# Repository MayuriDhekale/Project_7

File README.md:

# Project_7
<br>
<b>4-Layer STM32F407 Industrial Development Board</b>
<br>
Designed and developed a custom 4-layer STM32F407VGT6 development board intended as a flexible platform for embedded and industrial communication applications.
The board uses the STM32F407VGT6 microcontroller and includes USB Type-C, CAN, RS-485, UART, I²C, SPI, SWD, and GPIO interfaces. It also has a 3.3V power supply, reset and boot circuit, 8 MHz and 32.768 kHz crystals, and expansion headers for connecting external devices.

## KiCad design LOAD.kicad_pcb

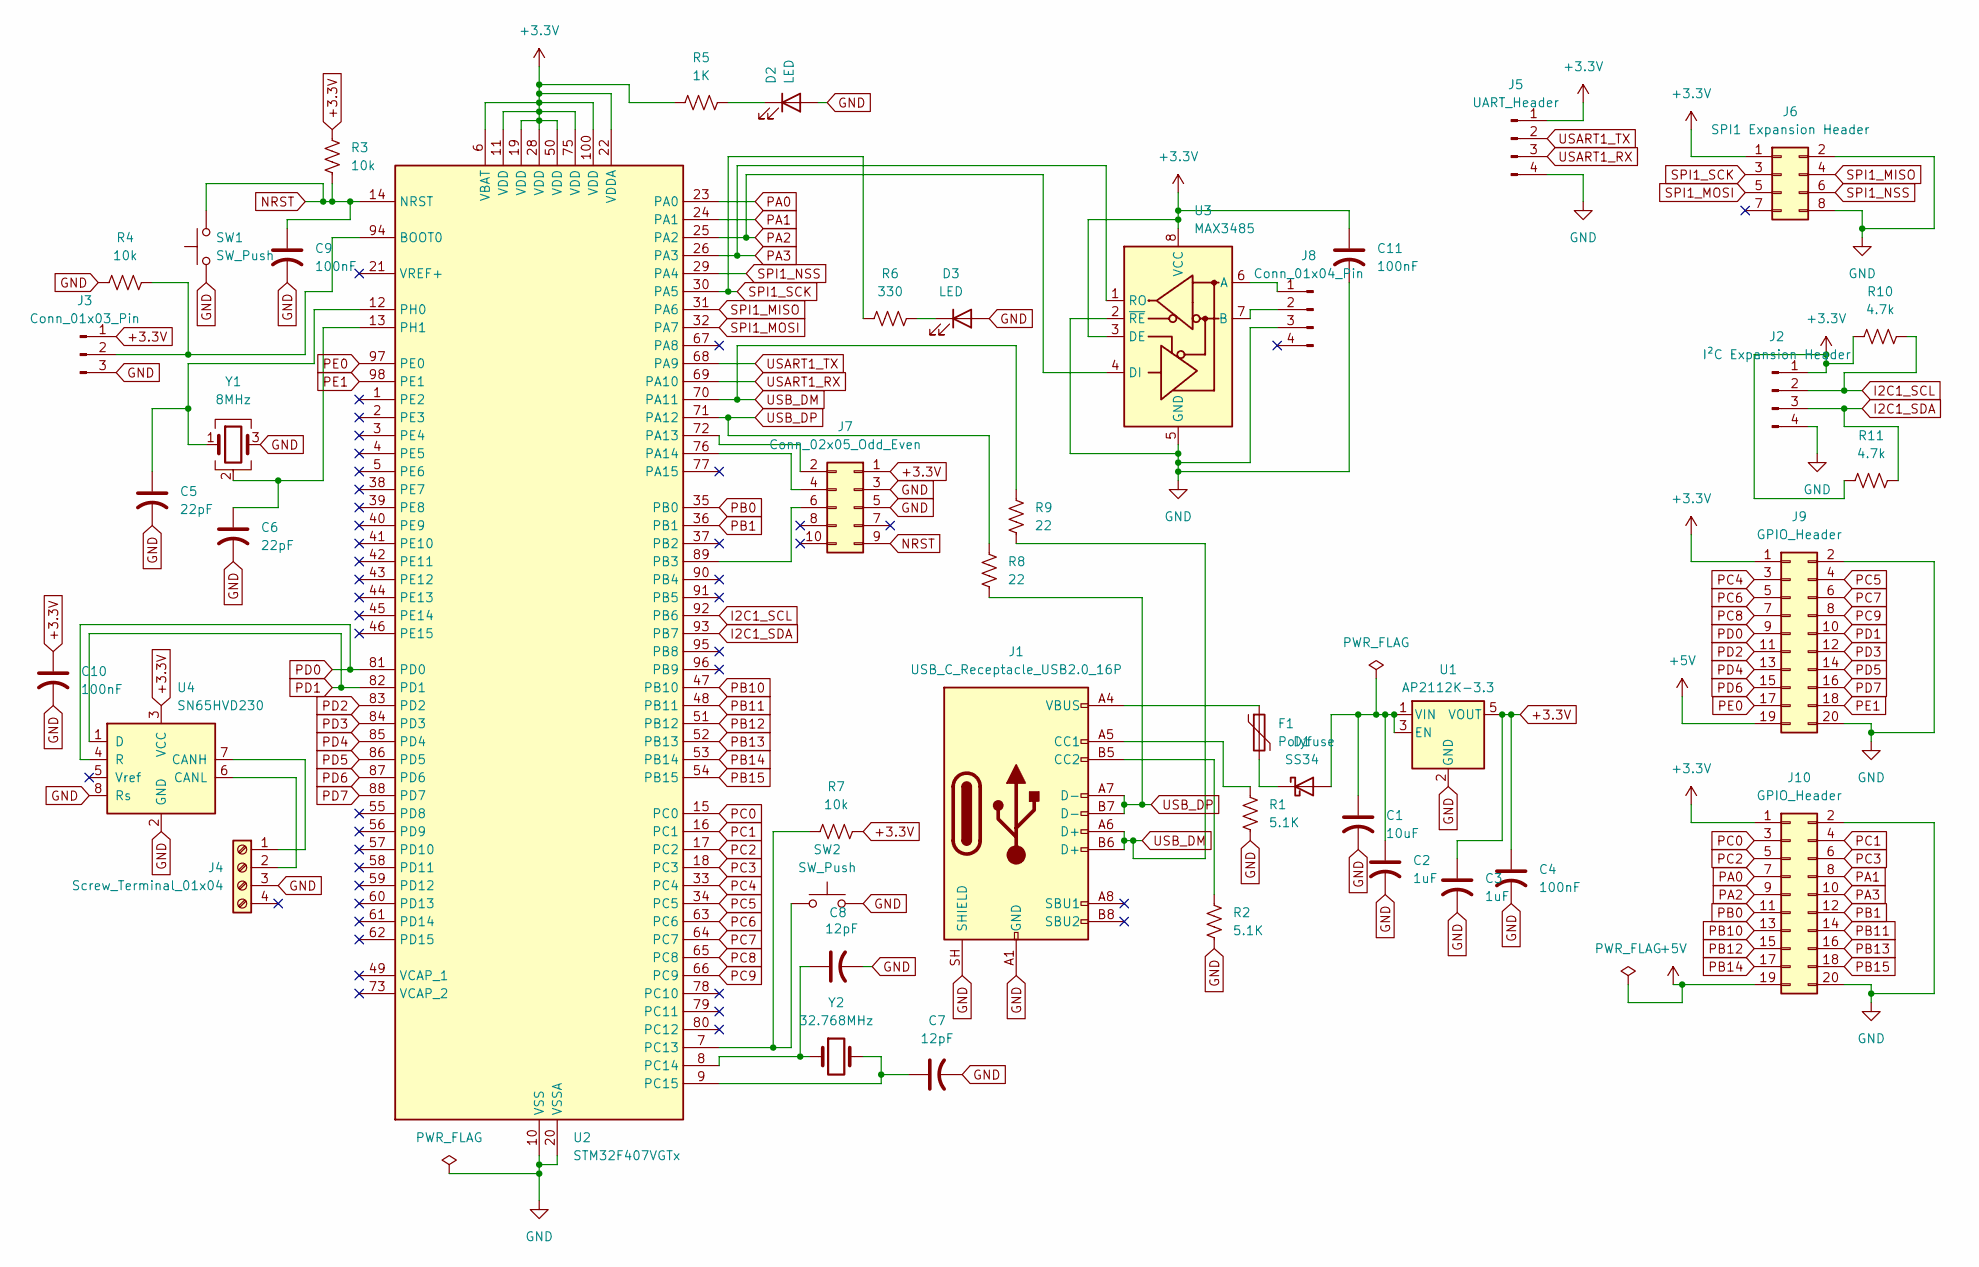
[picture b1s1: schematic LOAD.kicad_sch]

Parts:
C1: 10uF; C_0805_2012Metric
C2, C3: 1uF; C_0603_1608Metric
C4, C9, C10, C11: 100nF; C_0805_2012Metric
C5, C6: 22pF; C_0805_2012Metric
C7, C8: 12pF; C_0805_2012Metric
D1: SS34; D_SMA
D2, D3: LED; LED_0603_1608Metric
F1: Polyfuse; Fuse_1206_3216Metric
J1: USB_C_Receptacle_USB2.0_16P; USB_C_Receptacle_HRO_TYPE-C-31-M-12
J2: I²C Expansion Header; PinHeader_1x04_P2.54mm_Vertical
J3: Conn_01x03_Pin; PinHeader_1x03_P2.54mm_Vertical_SMD_Pin1Left
J4: Screw_Terminal_01x04; TerminalBlock_Phoenix_MKDS-1,5-4-5.08_1x04_P5.08mm_Horizont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
J5: UART_Header; PinHeader_1x04_P2.54mm_Vertical
J6: SPI1 Expansion Header; PinHeader_2x04_P2.54mm_Vertical
J7: Conn_02x05_Odd_Even; PinHeader_2x05_P2.54mm_Vertical
J8: Conn_01x04_Pin; PinHeader_1x04_P2.54mm_Vertical
J9, J10: GPIO_Header; PinHeader_2x10_P2.54mm_Vertical
R1, R2: 5.1K; R_0603_1608Metric
R3, R4, R7: 10k; R_0603_1608Metric
R5: 1K; R_0603_1608Metric
R6: 330; R_0603_1608Metric
R8, R9: 22; R_0603_1608Metric
R10, R11: 4.7k; R_0603_1608Metric
SW1, SW2: SW_Push; SW_SPST_TL3342
U1: AP2112K-3.3; SOT-23-5
U2: STM32F407VGTx; LQFP-100_14x14mm_P0.5mm
U3: MAX3485; SOIC-8_3.9x4.9mm_P1.27mm
U4: SN65HVD230; SOIC-8_3.9x4.9mm_P1.27mm
Y1: 8MHz; Crystal_SMD_3225-4Pin_3.2x2.5mm
Y2: 32.768MHz; Crystal_SMD_3215-2Pin_3.2x1.5mm

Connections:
+3.3V: C3.1, C4.1, C10.1, C11.1, J2.1, J3.1, J5.1, J6.1, J7.1, J9.1, J10.1, R3.1, R5.1, R7.2, R10.1, R11.1, U1.5 (VOUT), U2.6 (VBAT), U2.11 (VDD), U2.19 (VDD), U2.22 (VDDA), U2.28 (VDD), U2.50 (VDD), U2.75 (VDD), U2.100 (VDD), U3.3 (DE), U3.8 (VCC), U4.3 (VCC)
+5V: J9.19, J10.19
GND: C1.2, C2.2, C3.2, C4.2, C5.2, C6.2, C7.2, C8.2, C9.2, C10.2, C11.2, D2.2 (A), D3.2 (A), J1.A1 (GND), J1.A12 (GND), J1.B1 (GND), J1.B12 (GND), J1.SH (SHIELD), J2.4, J3.3, J4.3, J5.4, J6.2, J6.8, J7.3, J7.5, J8.3, J9.2, J9.20, J10.2, J10.20, R1.2, R2.2, R4.1, SW1.1, SW2.2, U1.2 (GND), U2.10 (VSS), U2.20 (VSSA), U2.27 (VSS), U2.74 (VSS), U2.99 (VSS), U3.2 (~RE), U3.5 (GND), U4.2 (GND), U4.8 (Rs), Y1.3
I2C1_SCL: J2.2, R10.2, U2.92 (PB6)
I2C1_SDA: J2.3, R11.2, U2.93 (PB7)
NRST: C9.1, J7.9, R3.2, SW1.2, U2.14 (NRST)
unnamed: C1.1, C2.1, D1.2 (A), U1.1 (VIN), U1.3 (EN)
unnamed: D1.1 (K), F1.2
unnamed: D2.1 (K), R5.2
unnamed: D3.1 (K), R6.2
unnamed: F1.1, J1.A4 (VBUS), J1.A9 (VBUS), J1.B4 (VBUS), J1.B9 (VBUS)
unnamed: J1.A5 (CC1), R1.1
unnamed: J1.B5 (CC2), R2.1
unnamed: J3.2, R4.2, U2.94 (BOOT0)
unnamed: J4.1, U4.7 (CANH)
unnamed: J4.2, U4.6 (CANL)
unnamed: J7.2, U2.72 (PA13)
unnamed: J7.4, U2.76 (PA14)
unnamed: J7.6, U2.89 (PB3)
unnamed: J8.1, U3.6 (A)
unnamed: J8.2, U3.7 (B)
unnamed: R7.1, SW2.1, U2.7 (PC13)
unnamed: C8.1, U2.8 (PC14), Y2.1
unnamed: C7.1, U2.9 (PC15), Y2.2
unnamed: C5.1, U2.12 (PH0), Y1.1
unnamed: C6.1, U2.13 (PH1), Y1.2 (G), Y1.4 (G)
PA0: J10.7, U2.23 (PA0)
PA1: J10.8, U2.24 (PA1)
PA2: J10.9, U2.25 (PA2), U3.4 (DI)
PA3: J10.10, U2.26 (PA3), U3.1 (RO)
PB0: J10.11, U2.35 (PB0)
PB1: J10.12, U2.36 (PB1)
PB10: J10.13, U2.47 (PB10)
PB11: J10.14, U2.48 (PB11)
PB12: J10.15, U2.51 (PB12)
PB13: J10.16, U2.52 (PB13)
PB14: J10.17, U2.53 (PB14)
PB15: J10.18, U2.54 (PB15)
PC0: J10.3, U2.15 (PC0)
PC1: J10.4, U2.16 (PC1)
PC2: J10.5, U2.17 (PC2)
PC3: J10.6, U2.18 (PC3)
PC4: J9.3, U2.33 (PC4)
PC5: J9.4, U2.34 (PC5)
PC6: J9.5, U2.63 (PC6)
PC7: J9.6, U2.64 (PC7)
PC8: J9.7, U2.65 (PC8)
PC9: J9.8, U2.66 (PC9)
PD0: J9.9, U2.81 (PD0), U4.4 (R)
PD1: J9.10, U2.82 (PD1), U4.1 (D)
PD2: J9.11, U2.83 (PD2)
PD3: J9.12, U2.84 (PD3)
PD4: J9.13, U2.85 (PD4)
PD5: J9.14, U2.86 (PD5)
PD6: J9.15, U2.87 (PD6)
PD7: J9.16, U2.88 (PD7)
PE0: J9.17, U2.97 (PE0)
PE1: J9.18, U2.98 (PE1)
SPI1_MISO: J6.4, U2.31 (PA6)
SPI1_MOSI: J6.5, U2.32 (PA7)
SPI1_NSS: J6.6, U2.29 (PA4)
SPI1_SCK: J6.3, R6.1, U2.30 (PA5)
USART1_RX: J5.3, U2.69 (PA10)
USART1_TX: J5.2, U2.68 (PA9)
USB_DM: J1.A6 (D+), J1.B6 (D+), R9.1, R9.2, U2.70 (PA11)
USB_DP: J1.A7 (D-), J1.B7 (D-), R8.1, R8.2, U2.71 (PA12)

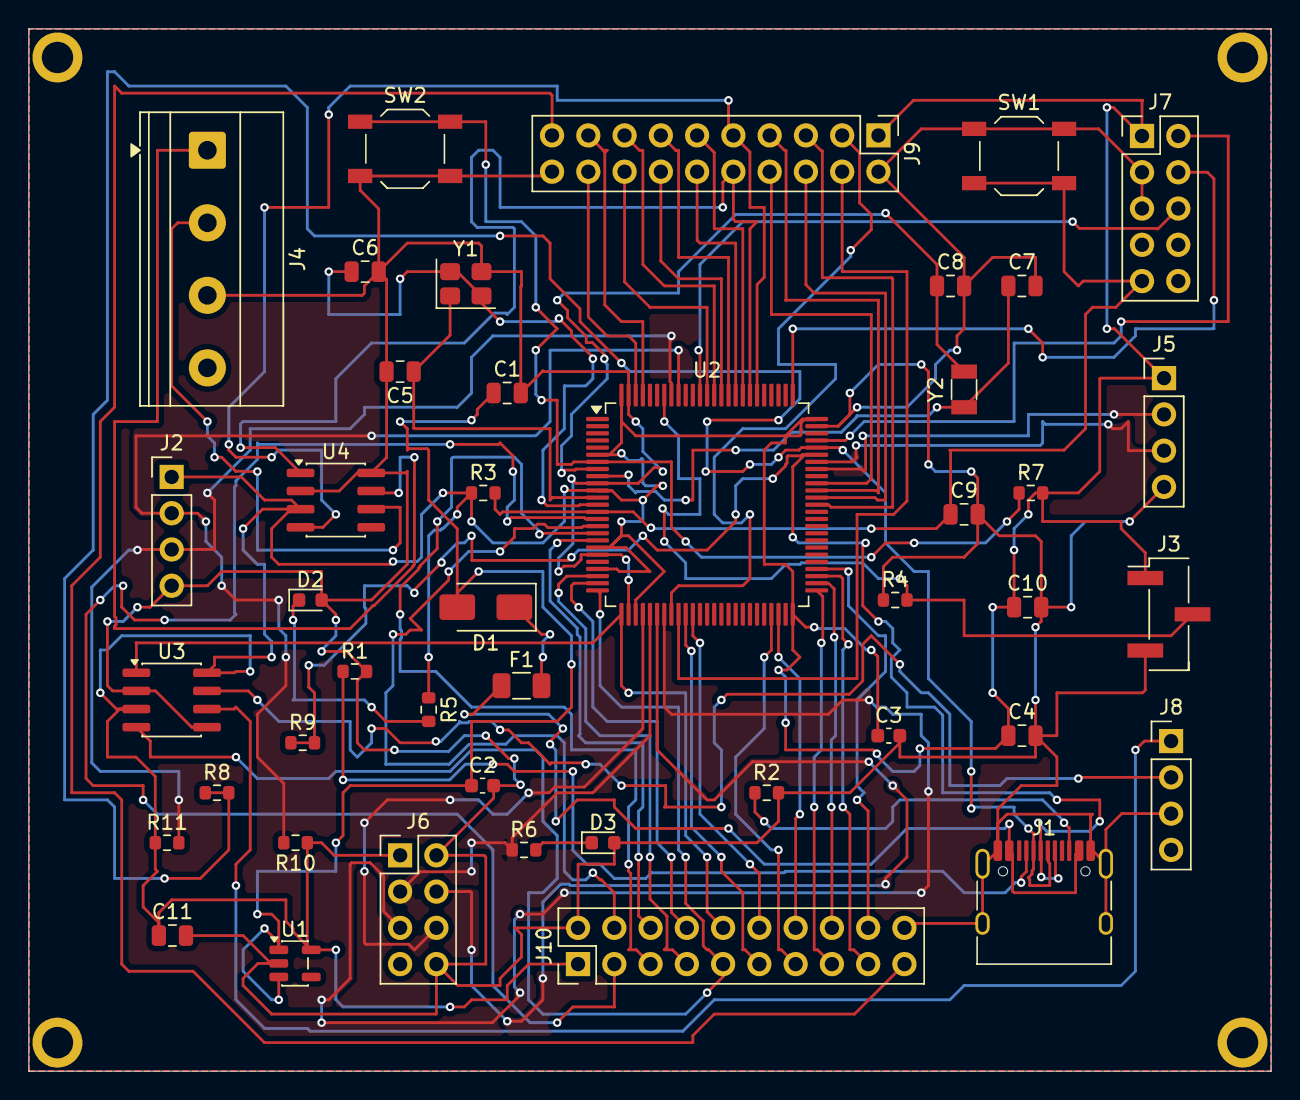
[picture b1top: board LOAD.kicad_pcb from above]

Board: 4 copper layers, 87.0 x 73.0 mm, 44 parts (0 on the bottom side), 66 nets.
